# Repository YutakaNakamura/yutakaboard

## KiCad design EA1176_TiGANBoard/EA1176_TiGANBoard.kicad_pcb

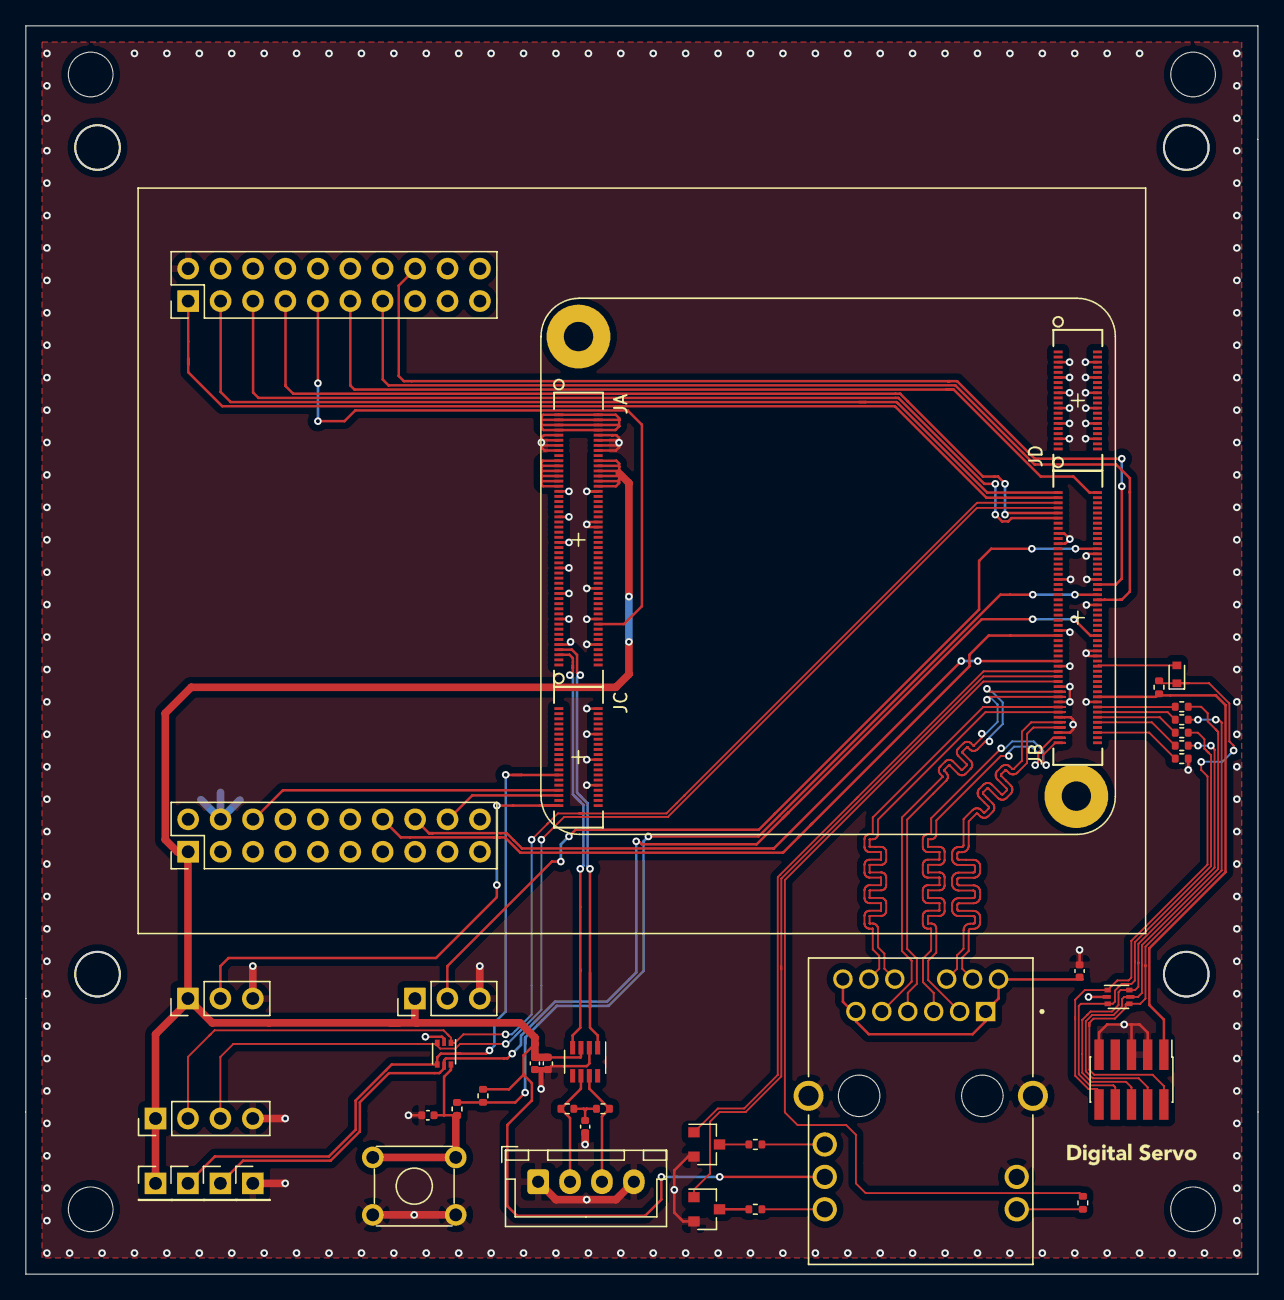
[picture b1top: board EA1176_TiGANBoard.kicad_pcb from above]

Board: 4 copper layers, 96.4 x 97.7 mm, 37 parts (0 on the bottom side), 58 nets.

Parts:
C1, C2, C3, C5: 0.1u; C_0402_1005Metric
C4: 1u; C_0402_1005Metric
D1: RB521S30T1G; D_SOD-523
D2, D3: PESD5V0L5UV; SOT-666
J1, J3: Conn_01x03; PinHeader_1x03_P2.54mm_Vertical
J2: L829-1J1T-43
J4: Conn_ARM_JTAG_SWD_10; PinHeader_2x05_P1.27mm_Vertical_SMD
J5: Conn_01x04; JST_XH_B4B-XH-A_1x04_P2.50mm_Vertical
J6: Conn_01x04; PinHeader_1x04_P2.54mm_Vertical
Q1, Q2: BSS138PW; SOT-23
R1, R2, R3: 150; R_0402_1005Metric
R4, R8: 10k; R_0402_1005Metric
R5: 100; R_0402_1005Metric
R6, R7: 60; R_0402_1005Metric
R9, R10, R11, R12: 50; R_0402_1005Metric
R13: 1k; R_0402_1005Metric
SW1: SW_MEC_5E; SW_TH_Tactile_Omron_B3F-10xx
TP1, TP2, TP3, TP4: TestPoint; PinHeader_1x01_P2.54mm_Vertical
U1: iMXRT1176uCOM
U2: BOOSTXL_3PhGaNInv_noTerminalBlock
U3: TCAN332G; SOT-23-8

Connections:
+3V3: C3.2, C4.2, J1.1, J2.16, J3.1, J6.1, R4.2, TP1.1, U1.20, U1.22, U1.24, U1.26, U1.28, U1.30, U2.1, U3.3
/ADC_U: U1.157, U2.17
/ADC_U1: J3.2, U1.124
/ADC_U2: J1.2, U1.239
/ADC_V: U1.167, U2.18
/ADC_VBUS: U1.233, U2.13
/ADC_W: U1.235, U2.19
/CAN1_RX: U1.95, U3.4
/CAN1_TX: U1.93, U3.1
/CAN+: J5.3, R6.1, U3.7
/CAN-: J5.2, R7.2, U3.6
/EA1176_SOM/Conn_RST: D1.1, D2.1, J4.10, R8.1
/EA1176_SOM/Conn_TCK: D2.5, J4.4, R9.2
/EA1176_SOM/Conn_TDI: D2.3, J4.8, R12.2
/EA1176_SOM/Conn_TDO: D2.6, J4.6, R11.2
/EA1176_SOM/Conn_TMS: D2.4, J4.2, R10.2
/EA1176_SOM/ETH1_LED_10_100: Q2.1, U1.171
/EA1176_SOM/ETH1_LED_1000: Q1.1, U1.173
/EA1176_SOM/ETH1_LED_ACT: R3.2, U1.175
/EA1176_SOM/ETH1_TRXN0: J2.10, U1.187
/EA1176_SOM/ETH1_TRXN1: J2.5, U1.181
/EA1176_SOM/ETH1_TRXN2: J2.2, U1.197
/EA1176_SOM/ETH1_TRXN3: J2.9, U1.191
/EA1176_SOM/ETH1_TRXP0: J2.11, U1.185
/EA1176_SOM/ETH1_TRXP1: J2.4, U1.179
/EA1176_SOM/ETH1_TRXP2: J2.3, U1.199
/EA1176_SOM/ETH1_TRXP3: J2.8, U1.193
/EA1176_SOM/JTAG_MOD: R13.1, U1.196
/EA1176_SOM/JTAG_TCK: R9.1, U1.186
/EA1176_SOM/JTAG_TDI: R12.1, U1.190
/EA1176_SOM/JTAG_TDO: R11.1, U1.192
/EA1176_SOM/JTAG_TMS: R10.1, U1.188
/EA1176_SOM/JTAG_VCC: J4.1, R8.2, U1.182
/EA1176_SOM/POR_B: D1.2, U1.170
/EA1176_SOM/VDD_1V8: U1.19, U1.21, U1.23, U1.25, U1.27, U1.29
/EA1176_SOM/VSYS_5V: U1.1, U1.2, U1.3, U1.4, U1.5, U1.6, U1.7, U1.8
/OT: U1.144, U2.27
/PWM_TRIG: D3.5, TP2.1, U1.158
/PWM_UH: U1.103, U2.21
/PWM_UL: U1.101, U2.22
/PWM_VH: U1.111, U2.23
/PWM_VL: U1.109, U2.24
/PWM_WH: U1.84, U2.25
/PWM_WL: U1.102, U2.26
/UART_RX: D3.1, J6.2, U1.105
/UART_TX: D3.3, J6.3, U1.107
/USER_GPIO: D3.4, TP3.1, U1.227
/USER_SW: R4.1, R5.2, U1.142
/USER_SW_BTN: C2.1, D3.6, R5.1, SW1.1, SW1.2
/nEnable: U1.138, U2.38
GND: C1.2, C2.2, C3.1, C4.1, C5.1, D2.2, D3.2, J1.3, J2.13, J2.S1, J2.S2, J3.3, J4.3, J4.5, J4.9, J5.1, J5.4, J6.4, Q1.2, Q2.2, R13.2, SW1.3, SW1.4, TP4.1, U1.9, U1.10, U1.11, U1.12, U1.13, U1.14, U1.15, U1.16, U1.31, U1.32, U1.41, U1.44, U1.46, U1.51, U1.61, U1.70, U1.71, U1.81, U1.82, U1.91, U1.92, U1.117, U1.121, U1.126, U1.135, U1.136, U1.146, U1.155, U1.164, U1.166, U1.169, U1.177, U1.183, U1.184, U1.189, U1.195, U1.202, U1.212, U1.222, U1.232, U1.245, U1.246, U1.251, U1.252, U1.257, U1.258, U1.263, U1.264, U1.269, U1.270, U1.275, U1.276, U2.12, U2.31, U3.2
unnamed: C1.1, J2.1, J2.6, J2.7, J2.12
unnamed: C5.2, R6.2, R7.1
unnamed: J2.14, R3.1
unnamed: J2.15, R2.1
unnamed: J2.17, R1.1
unnamed: Q1.3, R1.2
unnamed: Q2.3, R2.2

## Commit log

2021-04-01 [fix] CADを更新 V1.0 beta
2021-04-01 [fix] ゴミを削除
2021-04-05 [fix]RJ45のうねうねを追加
2021-04-09 [fix] logo/Gerber

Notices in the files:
parts and their libraries:
Copyright 2016 Accelerated Designs. All rights reserved.
